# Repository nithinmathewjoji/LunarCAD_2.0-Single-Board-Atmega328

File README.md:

# LunarCAD_2.0

## 📂 Repository Structure

- [KICAD_Files](https://github.com/nithinmathewjoji/LunarCAD_2.0/tree/master/KiCAD_Files)  
  KiCad project files for PCB design and electronics schematics.

- [LunarCAD_PPT](./LunarCAD_PPT)  
  Presentation materials and slides related to LunarCAD 2.0.

- [Schematics](./Schematics)  
  Circuit diagrams and supporting design documentation.

---

## 🚀 About

LunarCAD 2.0 continues the Lunarcad journey:
- Hands-on electronics design  
- Learning through collaboration  
- Building innovative projects together  

LunarCAD will continue to grow, and hopefully one day it will become one of the flagship events ever known by **IEEE** and the **College of Engineering Chengannur**.

---
## 📞 Contact

Connect with me on LinkedIn:  

---

## 📜 License

This project is released under the MIT License — feel free to use, modify, and share.

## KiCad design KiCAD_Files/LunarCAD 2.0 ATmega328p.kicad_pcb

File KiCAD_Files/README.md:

# LunaRduiNO

A custom Arduino Uno design project created and taught in college, built with KiCad.  
LunaRduiNO is a hands-on learning initiative that extends the classic Arduino Uno by exploring custom PCB design, schematic creation, and embedded hardware concepts.

---

## 📘 Project Overview

- **Platform:** KiCad  
- **Goal:** Teach students how to design and build a microcontroller board from scratch  
- **Focus Areas:**
  - Schematic design of Arduino Uno architecture
  - PCB layout and routing
  - Component selection and footprint assignment
  - Hands-on electronics learning

---

## 📂 Repository Contents

- `schematics/` → KiCad schematic files  
- `pcb_layout/` → PCB design files  
- `LunarCAD ATMEGA328.kicad_pro` → Main KiCad project file  download the .zip file and use it on kicad all files are inside it for youe recreation 
- `docs/` → Supporting notes, diagrams, and teaching materials  

---

## 🚀 Getting Started

1. Clone the repository:
   ```bash
   git clone https://github.com/nithinmathewjoji/LunarCAD_2.0.git

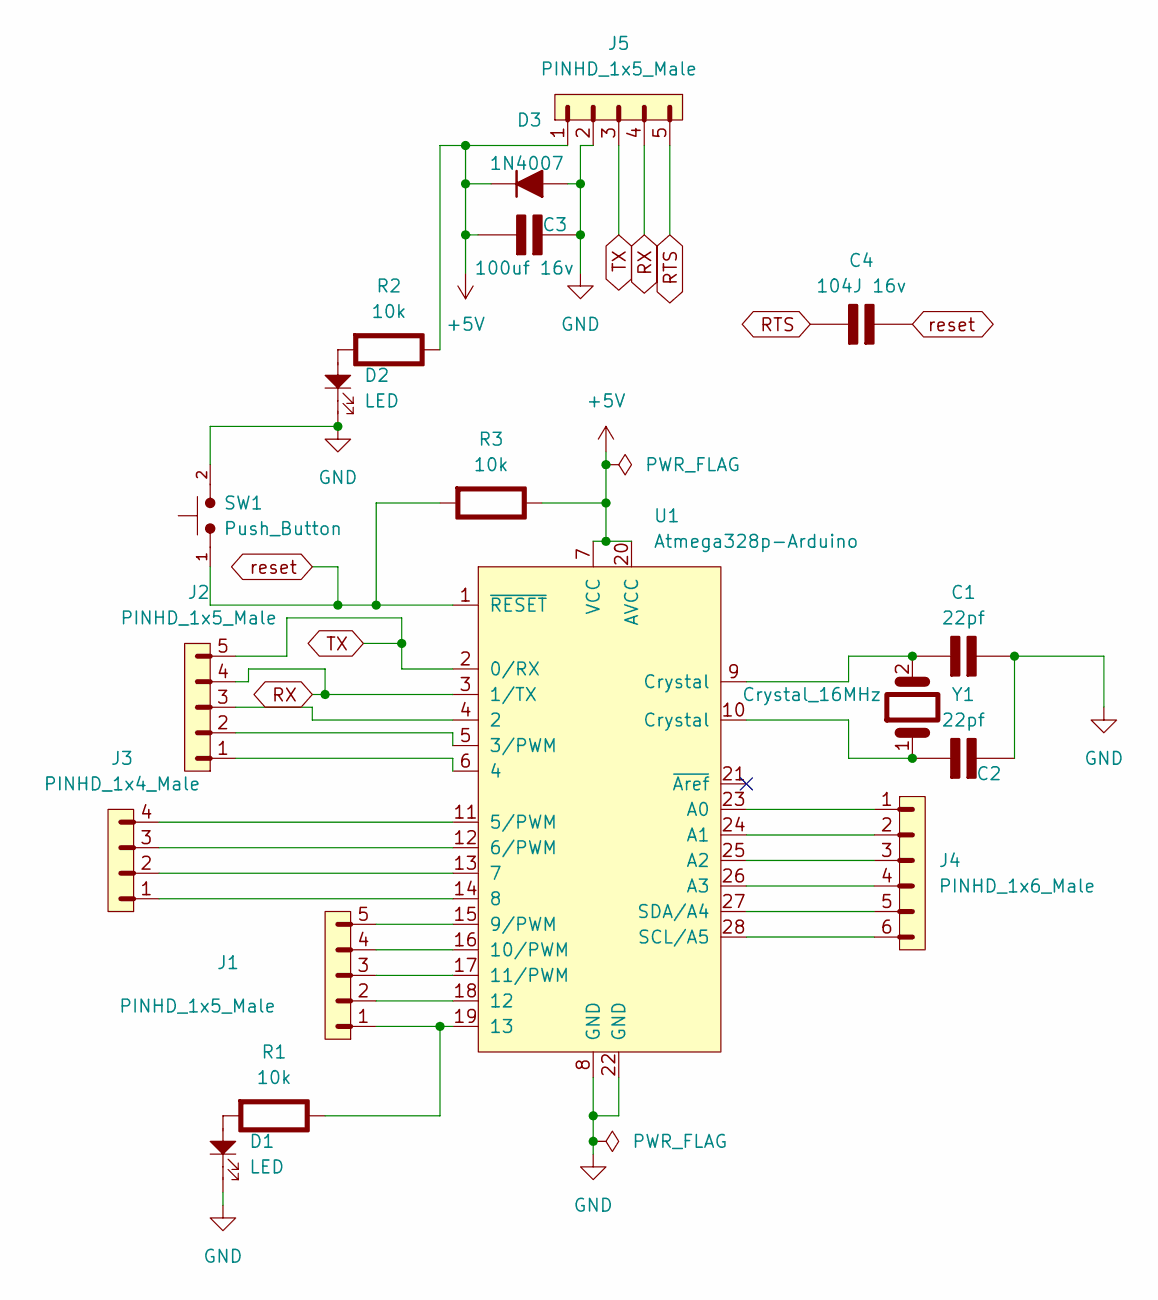
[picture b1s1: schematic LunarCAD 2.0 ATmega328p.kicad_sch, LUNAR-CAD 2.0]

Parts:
C1, C2: 22pf; C_Disc_D5.0mm_W2.5mm_P5.00mm; Rating V
C3: 100uf 16v; CP_Radial_Tantal_D5.5mm_P2.50mm; Rating V
C4: 104J 16v; C_Axial_L12.0mm_D7.5mm_P15.00mm_Horizontal; Rating V
D1, D2: LED; LED_D5.0mm
D3: 1N4007; D_DO-41_SOD81_P7.62mm_Horizontal
J1, J2, J5: PINHD_1x5_Male; PinHeader_1x05_P2.54mm_Vertical
J3: PINHD_1x4_Male; PinHeader_1x04_P2.54mm_Vertical
J4: PINHD_1x6_Male; PinHeader_1x06_P2.54mm_Vertical
R1, R2, R3: 10k; R_Axial_DIN0207_L6.3mm_D2.5mm_P10.16mm_Horizontal; Rating W
SW1: Push_Button; SW_PUSH_6mm
U1: Atmega328p-Arduino; DIP-28_W7.62mm_LongPads
Y1: Crystal_16MHz; Crystal_HC18-U_Vertical

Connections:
+5V: C3.1 (+), D3.1 (K), J5.1, R2.1 (+), R3.1 (+), U1.7 (VCC), U1.20 (AVCC)
GND: C1.2 (-), C2.2 (-), C3.2 (-), D1.1, D2.1, D3.2 (A), J5.2, SW1.2, U1.8 (GND), U1.22 (GND)
unnamed: C1.1 (+), U1.9 (Crystal), Y1.2
unnamed: C2.1 (+), U1.10 (Crystal), Y1.1
unnamed: J1.1, R1.1 (+), U1.19 (13)
unnamed: D1.2, R1.2 (-)
unnamed: D2.2, R2.2 (-)
unnamed: J2.3, U1.4 (2)
unnamed: J2.2, U1.5 (3/PWM)
unnamed: J2.1, U1.6 (4)
unnamed: J3.4, U1.11 (5/PWM)
unnamed: J3.3, U1.12 (6/PWM)
unnamed: J3.2, U1.13 (7)
unnamed: J3.1, U1.14 (8)
unnamed: J1.5, U1.15 (9/PWM)
unnamed: J1.4, U1.16 (10/PWM)
unnamed: J1.3, U1.17 (11/PWM)
unnamed: J1.2, U1.18 (12)
unnamed: J4.1, U1.23 (A0)
unnamed: J4.2, U1.24 (A1)
unnamed: J4.3, U1.25 (A2)
unnamed: J4.4, U1.26 (A3)
unnamed: J4.6, U1.28 (SCL/A5)
unnamed: J4.5, U1.27 (SDA/A4)
RTS: C4.1 (+), J5.5
RX: J2.4, J5.4, U1.3 (1/TX)
TX: J2.5, J5.3, U1.2 (0/RX)
reset: C4.2 (-), R3.2 (-), SW1.1, U1.1 (~RESET)

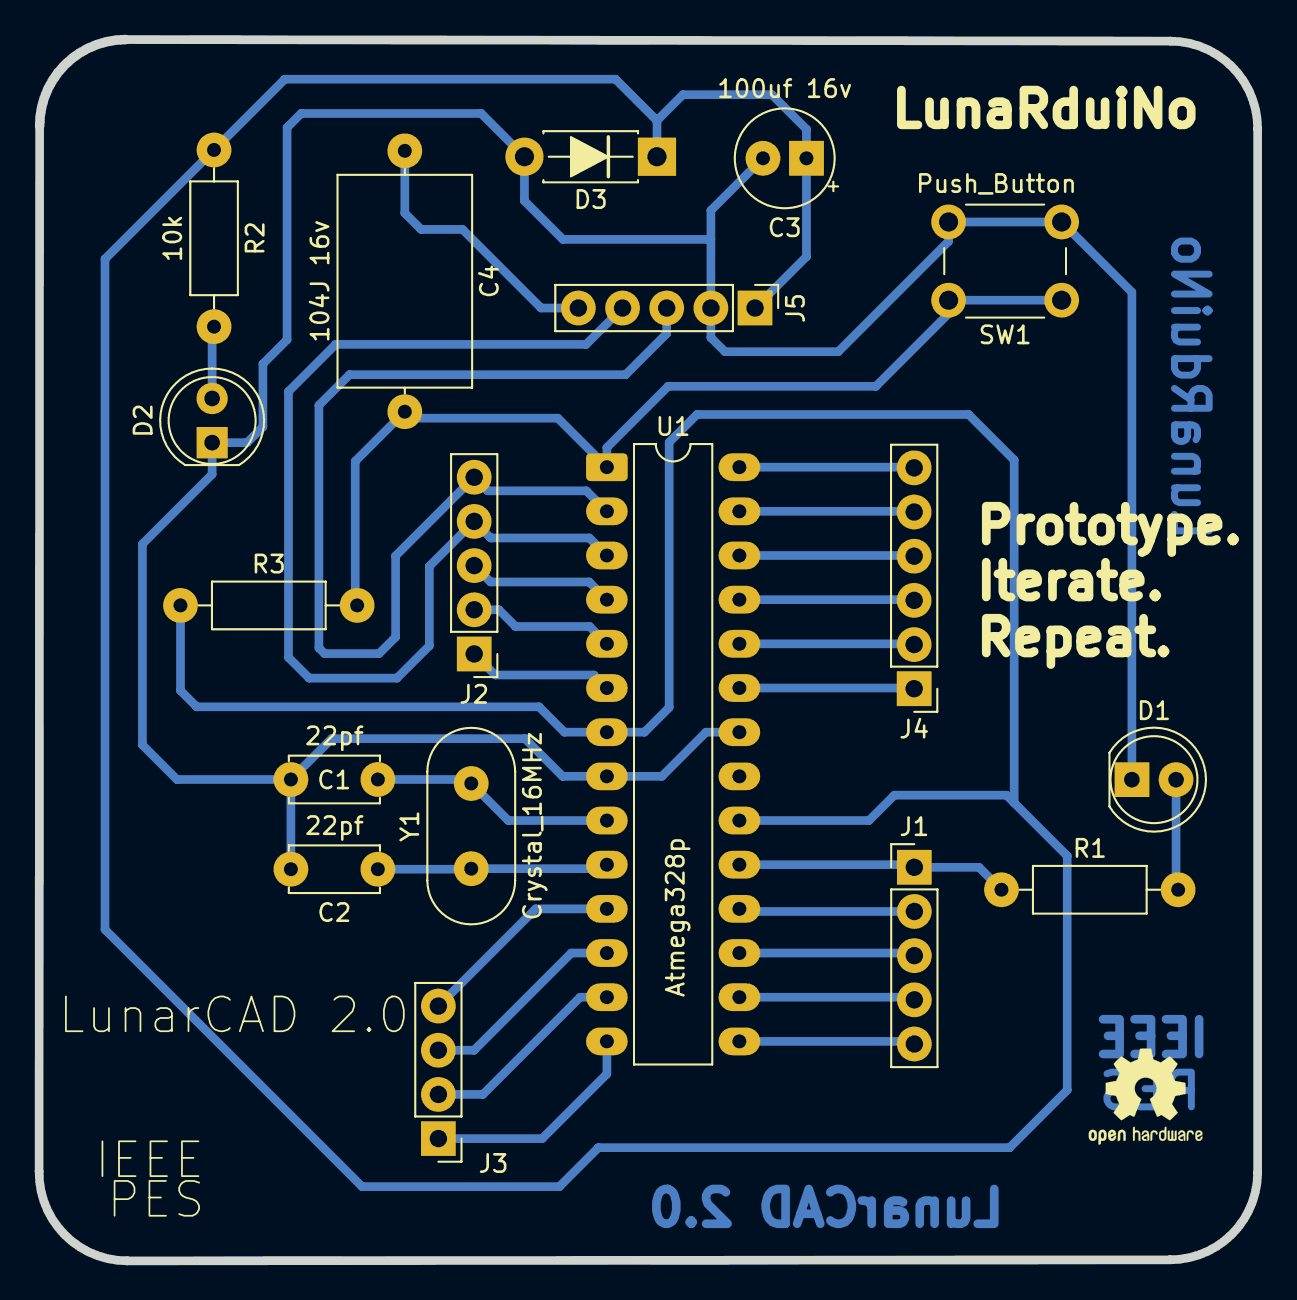
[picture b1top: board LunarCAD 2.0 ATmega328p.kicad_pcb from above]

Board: 2 copper layers, 70.1 x 70.2 mm, 18 parts (0 on the bottom side), 28 nets.

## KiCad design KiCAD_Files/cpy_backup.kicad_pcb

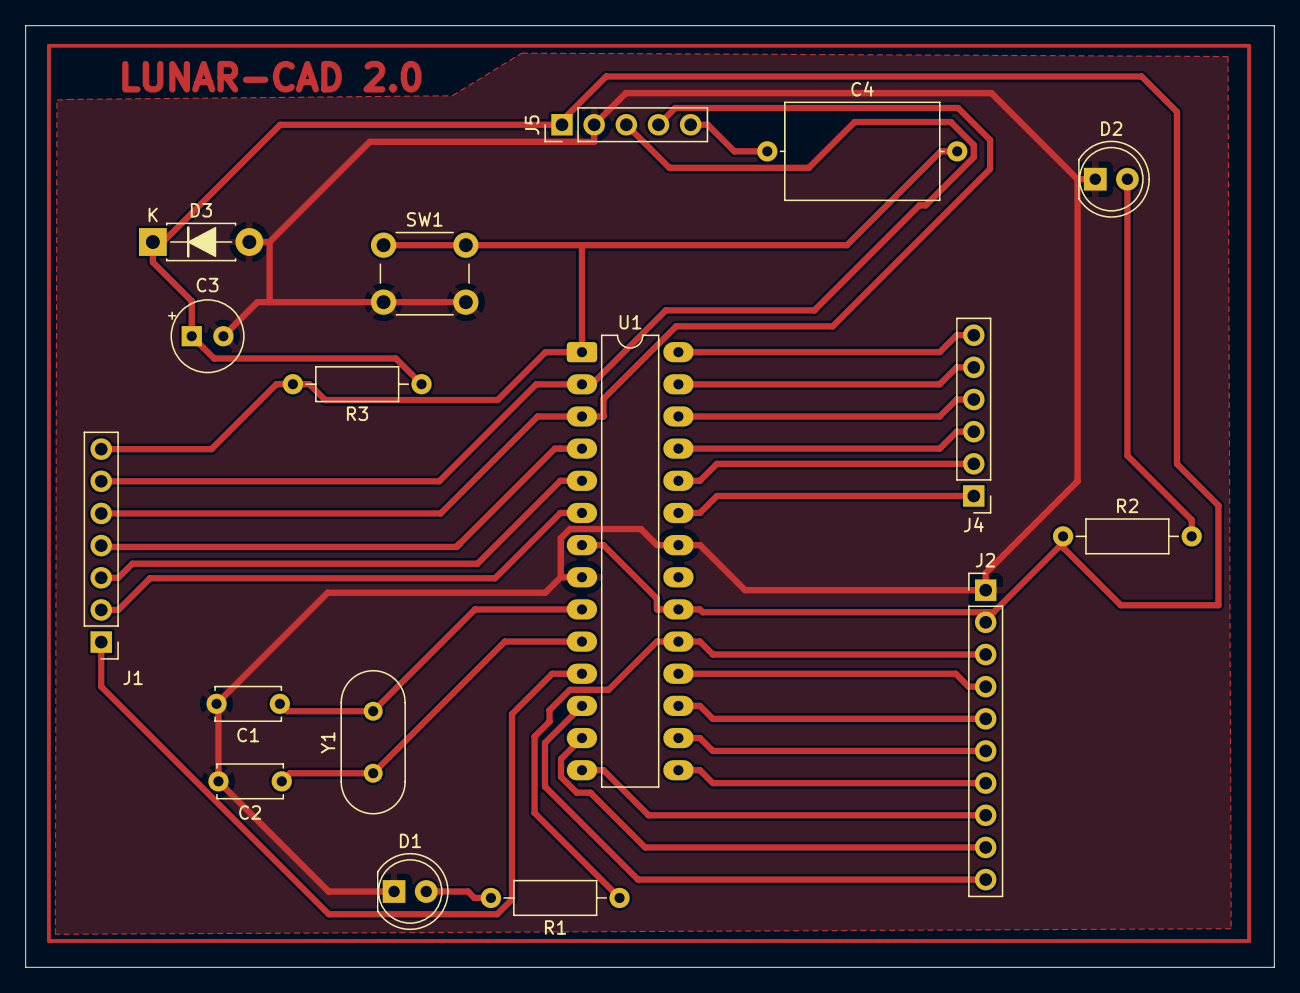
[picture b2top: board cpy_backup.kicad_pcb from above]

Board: 2 copper layers, 98.6 x 74.4 mm, 17 parts (0 on the bottom side), 28 nets.

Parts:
C1, C2: 22pf; C_Disc_D5.0mm_W2.5mm_P5.00mm
C3: 100uf 16v; CP_Radial_Tantal_D5.5mm_P2.50mm
C4: 104J 16v; C_Axial_L12.0mm_D7.5mm_P15.00mm_Horizontal
D1, D2: LED; LED_D5.0mm
D3: 1N4007; D_DO-41_SOD81_P7.62mm_Horizontal
J1: PINHD_1x7_Male; PinHeader_1x07_P2.54mm_Vertical
J2: PINHD_1x10_Male; PinHeader_1x10_P2.54mm_Vertical
J4: PINHD_1x6_Male; PinHeader_1x06_P2.54mm_Vertical
J5: PINHD_1x5_Male; PinHeader_1x05_P2.54mm_Vertical
R1, R2, R3: 10k; R_Axial_DIN0207_L6.3mm_D2.5mm_P10.16mm_Horizontal
SW1: Push_Button; SW_PUSH_6mm
U1: Atmega328p-Arduino; DIP-28_W7.62mm_LongPads
Y1: Crystal_16MHz; Crystal_HC18-U_Vertical

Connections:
+5V: C3.1 (+), D3.1 (K), J2.2, J5.1, R2.1 (+), R3.1 (+), U1.7 (VCC), U1.20 (AVCC)
GND: C1.2 (-), C2.2 (-), C3.2 (-), D1.1, D2.1, D3.2 (A), J2.1, J5.2, SW1.2, U1.8 (GND), U1.22 (GND)
unnamed: C1.1 (+), U1.9 (Crystal), Y1.2
unnamed: C2.1 (+), U1.10 (Crystal), Y1.1
unnamed: J2.3, R1.1 (+), U1.19 (13)
unnamed: D1.2, R1.2 (-)
unnamed: D2.2, R2.2 (-)
unnamed: J1.4, U1.4 (2)
unnamed: J1.3, U1.5 (3/PWM)
unnamed: J1.2, U1.6 (4)
unnamed: J1.1, U1.11 (5/PWM)
unnamed: J2.10, U1.12 (6/PWM)
unnamed: J2.9, U1.13 (7)
unnamed: J2.8, U1.14 (8)
unnamed: J2.7, U1.15 (9/PWM)
unnamed: J2.6, U1.16 (10/PWM)
unnamed: J2.5, U1.17 (11/PWM)
unnamed: J2.4, U1.18 (12)
unnamed: J4.1, U1.23 (A0)
unnamed: J4.2, U1.24 (A1)
unnamed: J4.3, U1.25 (A2)
unnamed: J4.4, U1.26 (A3)
unnamed: J4.6, U1.28 (SCL/A5)
unnamed: J4.5, U1.27 (SDA/A4)
RTS: C4.1 (+), J5.5
RX: J1.5, J5.4, U1.3 (1/TX)
TX: J1.6, J5.3, U1.2 (0/RX)
reset: C4.2 (-), J1.7, R3.2 (-), SW1.1, U1.1 (~RESET)

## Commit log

2025-11-30 Update link for project presentation PPTX
2025-11-30 Update README.md with project details
    Added project overview, contents, and getting started instructions.
2025-11-30 Update README with usage instructions for KiCad project
    Clarified instructions for using the main KiCad project file.
2025-11-30 Update KICAD_Files link in README
2025-11-30 Add contact section with LinkedIn link
    Added contact information and LinkedIn badge to README.
2025-12-03 Update issue templates
2025-12-03 Rename main KiCad project file in README
    Updated the main KiCad project file name in the README.
